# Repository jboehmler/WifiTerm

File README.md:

# WiFi Terminal

An ESP8266 runs as a WiFi access point and TLS server. A Python client on the PC
connects to it. In serial mode every key goes straight to a device on the ESP8266's
RS-232 port; Ctrl-] switches to command mode for the ESP's own settings.

Read `START-HERE.md` first.

## Layout

| Path | What |
|---|---|
```
wifiterm-<version>/
  README.md  START-HERE.md  CHANGELOG.md  VERSION
  firmware/   ESP8266 firmware (C): main/, Makefile, sdkconfig.defaults
  client/     PC terminal client (Python package)
  hardware/   rs232-shield/ (board + JLCPCB files), rs232-prototype.md (bench wiring)
  tools/      make-certs, test-certs, signing key + sign-fw, mock ESP, run-tests
  tests/      client, mock, firmware C tests, shared vectors
  docs/       protocol, decisions (ADRs), NOTES backlog, reviews, plans
  archive/    John's original files: 0.1.0 code and the original upload
```

| Path | What |
|---|---|
| `firmware/` | ESP8266_RTOS_SDK firmware (C). Build, flash, wiring: `firmware/README.md` |
| `client/` | PC client `wifiterm` (Python 3.10+, standard library only): `client/README.md` |
| `hardware/rs232-shield/` | RS-232 base board (TRS3243E, RJ45 console jack) and its JLCPCB files: `README.md` there |
| `hardware/rs232-prototype.md` | Bench wiring: MAX3232 module, TRS3221E/TRS3243E breakouts |
| `hardware/max3232-d1mini-wiring.md` | HiLetgo MAX3232 module to a D1 mini clone: 4 wires, diagram (`.svg`) |
| `tools/` | `make-certs.sh`, `test-certs.sh`, `make-signing-key.sh` + `sign-fw.sh` (firmware updates, ADR-0008), `mock_esp.py` (ESP simulator), `run-tests.sh` |
| `tests/` | pytest (client, mock), gcc tests (firmware C), shared test vectors |
| `archive/` | Originals, not built: `0.1.0/` (John's code), `wifiterm-0.1.0-original.tar` (as uploaded) |
| `docs/protocol.md` | Wire protocol and commands |
| `docs/decisions/` | Architecture decision records (ADRs) |
| `docs/NOTES.md` | Improvement and fix backlog, numbered |
| `CHANGELOG.md`, `VERSION` | Release history, current version (SemVer) |

Versions: `VERSION` numbers the whole package (0.0.0 is the first combined release). The
parts keep their own: firmware and client 0.2.0 (`FW_VERSION`, `client/wifiterm/__init__.py`),
board rev 0.2.

The firmware builds with ESP8266_RTOS_SDK v3.4 (make). The generic Docker build environment
for that SDK is a separate project, **esp8266-setup** (`esp make` in `firmware/`); it is not
part of this package.

## Quick start
```
bash tools/run-tests.sh                       # everything that can be tested without hardware
tools/make-certs.sh -p ~/wifiterm             # certificates (+ copies the PC's into the client profile)
pipx install ./client                         # the client
python3 tools/mock_esp.py --certs ../private/certs/localhost --device fortigate &   # try without hardware
wifiterm --host 127.0.0.1
```

## Working rules
See `START-HERE.md`. Private keys are never committed (`.gitignore`).

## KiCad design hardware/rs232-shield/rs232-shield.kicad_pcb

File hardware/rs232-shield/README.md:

# RS-232 base board, revision 0.2 (TRS3243E, RJ45 console jack)

- Date: 2026-10-21 (rev 0.1 was 2026-10-18: 55 x 36 mm, jack beside the D1 mini)
- Status: Design-rule check passes (copper); not yet built. For John's JLCPCB quote.

A 25.6 x 27.5 mm two-layer board that sits **under** the Wemos D1 mini, the same width as the
mini. The mini plugs in on top, antenna up; the board stops at the mini's first pins, so nothing
is under the antenna. The RJ45 jack is on the **underside**, directly below the mini's USB port,
opening the same way as USB. It takes a **standard straight 8-wire Ethernet cable** to a
Cisco-style RJ45 console port (FortiGate, Cisco, Juniper and most network gear).

```
side view          D1 mini (antenna end left, USB right)
  antenna ->  =====[###############]=[USB]
                     |  sockets  |
                   ===============        <- this board, SMT parts on top
                          [ RJ45 ]=>      <- jack on the underside, opening below USB
```

Picture book (board top and bottom, parts layout, four 3D views of the assembled unit):
[rs232-shield-views.docx](rs232-shield-views.docx), made by `doc/make_doc.py` from the JLCPCB files.

Top (parts side, under the mini): [view-top.png](jlcpcb/view-top.png).
Underside (jack side): [view-bottom.png](jlcpcb/view-bottom.png).

## Files for JLCPCB (`jlcpcb/`)

| File | Upload as |
|---|---|
| `rs232-shield-gerbers.zip` | Gerber files (copper, mask, paste, silk, outline, drill) |
| `bom.csv` | BOM (SMT parts, LCSC numbers) |
| `cpl.csv` | Pick-and-place (CPL) |
| `view-top.png`, `view-bottom.png` | Preview only, not uploaded |

## Ordering

1. Upload the Gerber zip. Defaults are right: 2 layers, 1.6 mm, any colour. Quantity 5 is
   the minimum.
2. Turn on **PCB Assembly**, **top side**, then upload `bom.csv` and `cpl.csv`.
3. On the placement preview, check **U1's pin 1** (dot or chamfer) sits at the pad marked with
   the small triangle, top-left of U1. KiCad and JLCPCB sometimes disagree on rotation for
   SSOP parts; if it is off, rotate U1 in the preview until it matches.
4. Parts are JLCPCB "basic" except U1 (extended, one-time loading fee). LCSC stock of U1
   (C544326) was 153 on 2026-10-11.
5. Buy the RJ45 jack with the order (JLCPCB parts or LCSC): **CONNFLY DS1128-09-S8B8S,
   LCSC C77851**. Plain jack (no Ethernet transformer, which would block RS-232); LEDs unused.

## Parts

| Ref | Part | LCSC | Fitted by |
|---|---|---|---|
| U1 | TI TRS3243ECDBR, RS-232 3 drivers / 5 receivers, SSOP-28 | C544326 | JLCPCB |
| C1-C5 | 100 nF X7R 0603 (charge pump, bypass) | C14663 | JLCPCB |
| C6 | 1 uF 0603 (bypass; TI requires 1 uF for the IEC ESD rating) | C15849 | JLCPCB |
| R1, R2 | 10k 0603, pull-ups on D7 and D6 (chip outputs float when it is off) | C25804 | JLCPCB |
| R3 | 10k 0603, pull-down on D1 (chip off through reset) | C25804 | JLCPCB |
| J1 | RJ45 jack, CONNFLY DS1128-09-S8B8S | C77851 | John |
| J2, J3 | 2 x 8-pin female sockets, 2.54 mm (come with the D1 mini) | - | John |

## Connections

| D1 mini | Board | Function |
|---|---|---|
| D8 (GPIO15) | U1 DIN1 | Data to the device |
| D7 (GPIO13) | U1 ROUT1, R1 pull-up | Data from the device |
| D5 (GPIO14) | U1 DIN2 | RTS out (future `flow=rtscts`) |
| D6 (GPIO12) | U1 ROUT2, R2 pull-up | CTS in (future `flow=rtscts`) |
| D1 (GPIO5) | U1 FORCEOFF + FORCEON, R3 pull-down | Chip on when high (`CHIP_POWER_ON_LEVEL 1`) |
| D2 (GPIO4) | U1 INVALID | Low when nothing drives any RS-232 input (cable detect) |
| 3V3, G | U1 VCC, ground | Power |

| RJ45 pin | Device console port pin (straight cable) | Board signal |
|---|---|---|
| 1 | RTS (device output) | U1 RIN2 -> our CTS |
| 2 | DTR (device output) | U1 RIN3 (spare; helps cable detect) |
| 3 | TxD (device output) | U1 RIN1 -> our RX |
| 4, 5 | GND | GND |
| 6 | RxD (device input) | U1 DOUT1 <- our TX |
| 7 | DSR (device input) | U1 DOUT3, always on (DIN3 grounded) |
| 8 | CTS (device input) | U1 DOUT2 <- our RTS |

The device-side pinout is the common Cisco console pinout (Juniper documents the same:
1 RTS, 2 DTR, 3 TxD, 4/5 GND, 6 RxD, 7 DSR/DCD, 8 CTS). Do **not** plug this jack into an
Ethernet switch port.

Checked 2026-10-24 against vendor documents: Juniper and Extreme Networks publish exactly this pinout
(1 RTS out, 2 DTR out, 3 TxD out, 4/5 GND, 6 RxD in, 7 DSR in, 8 CTS in); Fortinet's console cable
uses 3 = device TxD, 6 = device RxD, 5 = GND (FortiGate 9600 8N1, no flow control); HP ProCurve
2810's cable traces out the same. Exception: APC UPS RJ45 serial ports are not console ports, and
a console cable can switch the UPS off (APC FAQ FA156800). Don't plug in there.

## Assembly by John
1. Fit J1 on the **underside** (the side with the "WIFITERM RS-232 v0.2" text), opening toward the
   board edge, and solder its pins on the top side.
2. Solder the two female sockets J2, J3 on the **top** side (the side with U1).
3. Solder the D1 mini's male pins to the mini, pins pointing down, and plug it in with its USB end
   over the jack (5V and 3V3 at the jack end, TX/RST at the far end).

There are no vias under the jack (keep-out), so its metal case cannot short anything.

## Firmware
- Set `CHIP_POWER_ON_LEVEL 1` in `firmware/main/config.h`.
- RTS/CTS (D5/D6) and cable detect (D2) are wired but not yet used by the firmware.

## How it is made
`make_board.py` (KiCad 7 Python API) holds the parts, positions and netlist; `build.sh`
places, routes with Freerouting 1.9.0, pours ground on both layers, runs KiCad's
design-rule check (`drc-report.txt`) and writes `jlcpcb/`. There is no KiCad schematic
file; the netlist in `make_board.py` and the tables above are the schematic. Open
`rs232-shield.kicad_pcb` in KiCad to inspect or edit the layout.

DRC: 0 copper errors, 0 unconnected. Remaining warnings are silkscreen only (reference
labels clipped by pads, D1 mini outline drawn past the board edge), which JLCPCB clips.

## Checked, and not yet checked
- Checked: TRS3243E pin functions against TI's datasheet; every pad's net against the
  netlist (script check, 0 mismatches); Gerbers rendered back with gerbv.
- Inferred, please confirm on JLCPCB's 3D preview: the RJ45 opening faces the board edge
  (USB end) on the underside. The KiCad footprint marks the front only indirectly (silkscreen
  left open on that side).
- Inferred: the board's pin spacing (22.86 mm between rows) matches your D1 mini clones. Worth
  checking with a ruler before ordering.
- Checked 2026-10-25 against the CONNFLY drawing (`hardware/reference/connfly-ds1128-09-rj45-C77851.pdf`):
  DS1128-09-S8B8S has no Ethernet transformer (8 contacts straight to pins, plus 4 LED pins and 2
  shell tabs). Every footprint dimension matches: pins 1.02 mm pitch, rows 1.78 mm apart, 7.14 mm
  span, 0.9 mm holes; pegs 3.25 mm, 12.7 mm apart; shell tabs 1.8 mm, 16.26 mm apart; LED holes
  9.14 / 13.72 mm. The opening is on the peg side, so on this board it is flush with the USB-end
  edge. The plug latch faces away from the board (down, with the jack on the underside).
  Pins are 2.8 mm long, so they stick out about 1.2 mm on the top side under the D1 mini.
  The green and yellow LEDs (pads 9-12) are not connected.
- Alternative jack, LCSC C708625 (Ruichuan RCH-56-31, all plastic, no LEDs, no shell;
  `hardware/reference/ruichuan-rch-56-31-rj45-C708625.pdf`): same 8-pin pattern, but its pegs are
  12.6 mm apart (3.2 mm pegs in our 3.25 mm holes 12.7 mm apart), so it fits with almost no
  clearance. The LED and shell holes would just be empty.
- Not built or powered.

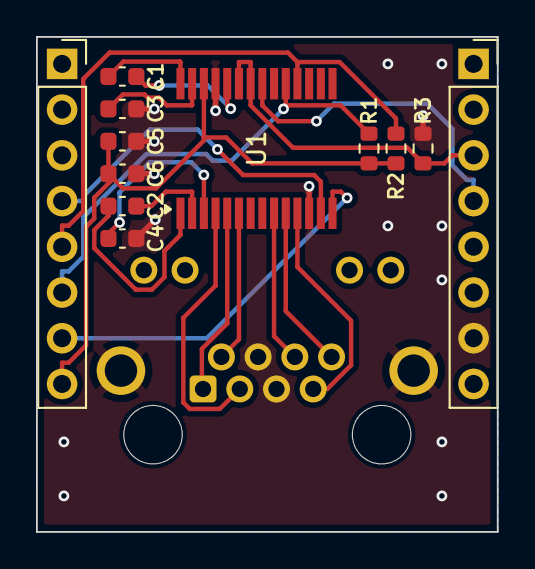
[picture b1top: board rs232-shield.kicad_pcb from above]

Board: 2 copper layers, 25.6 x 27.5 mm, 13 parts (1 on the bottom side), 20 nets.

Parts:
C1, C2, C3, C4, C5: 100nF; C_0603_1608Metric
C6: 1uF; C_0603_1608Metric
J1: DS1128-09-S8B8S; RJ45_Connfly_DS1128-09-S8xx-S_Horizontal
J2: D1 mini left row; PinSocket_1x08_P2.54mm_Vertical
J3: D1 mini right row; PinSocket_1x08_P2.54mm_Vertical
R1, R2, R3: 10k; R_0603_1608Metric
U1: TRS3243ECDBR; SSOP-28_5.3x10.2mm_P0.65mm

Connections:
+3V3: C5.1, C6.1, J2.8, R1.1, R2.1, U1.26
C1N: C1.2, U1.24
C1P: C1.1, U1.28
C2N: C2.2, U1.2
C2P: C2.1, U1.1
CABLE: J3.4, U1.21
CHIP_ON: J3.3, R3.1, U1.22, U1.23
CTS: J2.5, R2.2, U1.18
DEV_RX: J2.6, R1.2, U1.19
DEV_TX: J2.7, U1.14
GND: C3.2, C4.2, C5.2, C6.2, J1.4, J1.5, J1.SH, J3.7, R3.2, U1.12, U1.25
RS_CTS: J1.1, U1.5
RS_DSR: J1.2, U1.6
RS_DTR: J1.7, U1.11
RS_RTS: J1.8, U1.10
RS_RXD: J1.3, U1.4
RS_TXD: J1.6, U1.9
RTS: J2.4, U1.13
VNEG: C4.1, U1.3
VPOS: C3.1, U1.27

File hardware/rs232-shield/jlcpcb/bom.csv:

Comment,Designator,Footprint,LCSC Part #
100nF,"C1,C2,C3,C4,C5",C_0603_1608Metric,C14663
1uF,C6,C_0603_1608Metric,C15849
10k,"R1,R2,R3",R_0603_1608Metric,C25804
TRS3243ECDBR,U1,SSOP-28_5.3x10.2mm_P0.65mm,C544326

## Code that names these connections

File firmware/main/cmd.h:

/**
 * @file cmd.h
 * @brief ESP command handler (docs/protocol.md, "Commands"): parses CMD text, calls the
 *        hardware through an ops table, and writes the RESP text.
 * @details Portable C99 with no ESP headers, so it is unit-tested on the PC with gcc and
 *          checked against the same vectors as the Python mock (tests/vectors/commands.txt).
 */
#ifndef CMD_H
#define CMD_H

#include <stddef.h>
#include <stdint.h>

#include "cabledet.h"

/** @brief Device flow control modes. */
typedef enum {
    FLOW_NONE = 0, /**< No flow control. */
    FLOW_RTSCTS,   /**< RTS/CTS on GPIOs (needs pins; not in 0.2.0). */
    FLOW_XONXOFF,  /**< XON/XOFF in the data stream. */
} flow_t;

/** @brief Device serial settings. */
typedef struct {
    uint32_t baud;  /**< Bits per second, UART_BAUD_MIN..UART_BAUD_MAX. */
    uint8_t bits;   /**< Data bits 5..8. */
    char parity;    /**< 'N', 'E' or 'O'. */
    uint8_t stop2;  /**< Stop bits times two: 2, 3 or 4 (1, 1.5, 2). */
    uint8_t flow;   /**< flow_t. */
} uart_cfg_t;

/** @brief Lowest baud rate accepted. */
#define UART_BAUD_MIN 300
/** @brief Highest baud rate accepted. */
#define UART_BAUD_MAX 921600
/** @brief Longest `uart break`, ms. */
#define BREAK_MS_MAX 5000
/** @brief Default `uart break`, ms. */
#define BREAK_MS_DEFAULT 250
/** @brief Longest SSID (802.11 limit). */
#define SSID_MAX 32
/** @brief Shortest WPA2 passphrase. */
#define PASS_MIN 8
/** @brief Longest WPA2 passphrase. */
#define PASS_MAX 63

/** @brief Factory serial settings: 9600,8,N,1,none (FortiGate console default). */
extern const uart_cfg_t UART_CFG_DEFAULT;

/**
 * @brief Format settings as "9600,8,N,1,none".
 * @param c Settings.
 * @param buf Destination.
 * @param n Size of @p buf.
 * @return @p buf.
 */
const char *uart_cfg_text(const uart_cfg_t *c, char *buf, size_t n);

/**
 * @brief Check that stored settings are sane (e.g. after reading NVS).
 * @param c Settings.
 * @return 1 if valid.
 */
int uart_cfg_valid(const uart_cfg_t *c);

/**
 * @brief Hardware and storage operations the commands need. The firmware fills this with
 *        real functions; the host test fills it with fakes that record calls.
 * @details Functions return 0 on success, nonzero on failure, unless noted.
 */
typedef struct {
    void *ctx;                                                  /**< Passed to every call. */
    int (*uart_apply)(void *ctx, const uart_cfg_t *c);          /**< Use settings now. */
    int (*uart_save)(void *ctx, const uart_cfg_t *c);           /**< Store as boot settings. */
    int (*uart_saved)(void *ctx, uart_cfg_t *c);                /**< Read boot settings. */
    int (*uart_break)(void *ctx, unsigned ms);                  /**< Send a line break. */
    int (*uart_power)(void *ctx, int mode);                     /**< Set power_mode_t (off/on/auto). */
    int (*power_save)(void *ctx, int mode);                     /**< Store the boot power mode. */
    int (*power_saved)(void *ctx, int *mode);                   /**< Read the boot power mode. */
    void (*power_status)(void *ctx, char *buf, size_t n);       /**< "chip=on|off cable=none|console|unknown". */
    void (*wifi_get)(void *ctx, char *ssid, size_t n, unsigned *channel); /**< Current AP. */
    int (*wifi_save)(void *ctx, const char *ssid, const char *pass, unsigned channel); /**< 0 = keep channel. */
    void (*log_level)(void *ctx, char level);                   /**< 'E','W','I','D', or 0 = off. */
    int (*set_reboot_on_disconnect)(void *ctx, int on);         /**< Save the R3 setting. */
    void (*reboot)(void *ctx);                                  /**< Restart soon (after the reply). */
    void (*info)(void *ctx, char *buf, size_t n);               /**< "fw=.. sdk=.. heap=.. uptime=.. reset=..". */
    int (*bat_read)(void *ctx, int *mv, int *cal);              /**< Calibrated mV and cal; -1 = no battery. */
    int (*bat_cal_save)(void *ctx, int cal);                    /**< Use and store a calibration (per mille). */
    int (*fw)(void *ctx, char **w, int nw, char *reply, size_t n); /**< `fw ...` (fwup_cmd); 1 OK, 0 ERR. */
    int has_power;   /**< Nonzero if a chip power pin is configured. */
    int has_rtscts;  /**< Nonzero if RTS/CTS pins are configured. */
    int has_cabledetect; /**< Nonzero if the chip's INVALID output is wired (enables `uart power auto`). */
    int has_ota;     /**< Nonzero with the two-slot flash layout (enables `fw`, NOTES I-25). */
} cmd_ops_t;

/** @brief Command handler state: the serial settings and power mode in use. */
typedef struct {
    uart_cfg_t active; /**< Active (maybe unsaved) settings. */
    int power_mode;    /**< Active power_mode_t (maybe unsaved). */
} cmd_state_t;

/**
 * @brief Factory power mode: auto with a cable-detect pin, else on.
 * @param ops Operations (has_cabledetect is used).
 * @return power_mode_t.
 */
int cmd_power_default(const cmd_ops_t *ops);

/**
 * @brief Power mode to use at boot or `uart revert`, from what NVS held.
 * @details With cable detect, `on` is a temporary override (John 2026-10-25) and is never
 *          restored; neither is `auto` without cable detect. Both fall back to the default.
 * @param ops Operations (has_cabledetect is used).
 * @param found Nonzero if a saved mode was read.
 * @param mode The saved mode.
 * @return power_mode_t.
 */
int cmd_power_boot(const cmd_ops_t *ops, int found, int mode);

/** @brief Longest RESP text written by cmd_run. */
#define CMD_REPLY_MAX 200

/**
 * @brief Run one command.
 * @param st State (active settings).
 * @param ops Hardware operations.
 * @param text Command text without the sequence number, e.g. "uart get".
 * @param reply Receives the reply text (without "OK"/"ERR").
 * @param n Size of @p reply (CMD_REPLY_MAX is enough).
 * @return 1 for OK, 0 for ERR.
 */
int cmd_run(cmd_state_t *st, const cmd_ops_t *ops, const char *text, char *reply, size_t n);

/**
 * @brief Build the HELLO capability list for this firmware and its pin settings.
 * @param ops Operations (has_power, has_rtscts, has_cabledetect are used).
 * @param buf Destination.
 * @param n Size of @p buf.
 * @return @p buf.
 */
const char *cmd_caps(const cmd_ops_t *ops, char *buf, size_t n);

#endif /* CMD_H */
